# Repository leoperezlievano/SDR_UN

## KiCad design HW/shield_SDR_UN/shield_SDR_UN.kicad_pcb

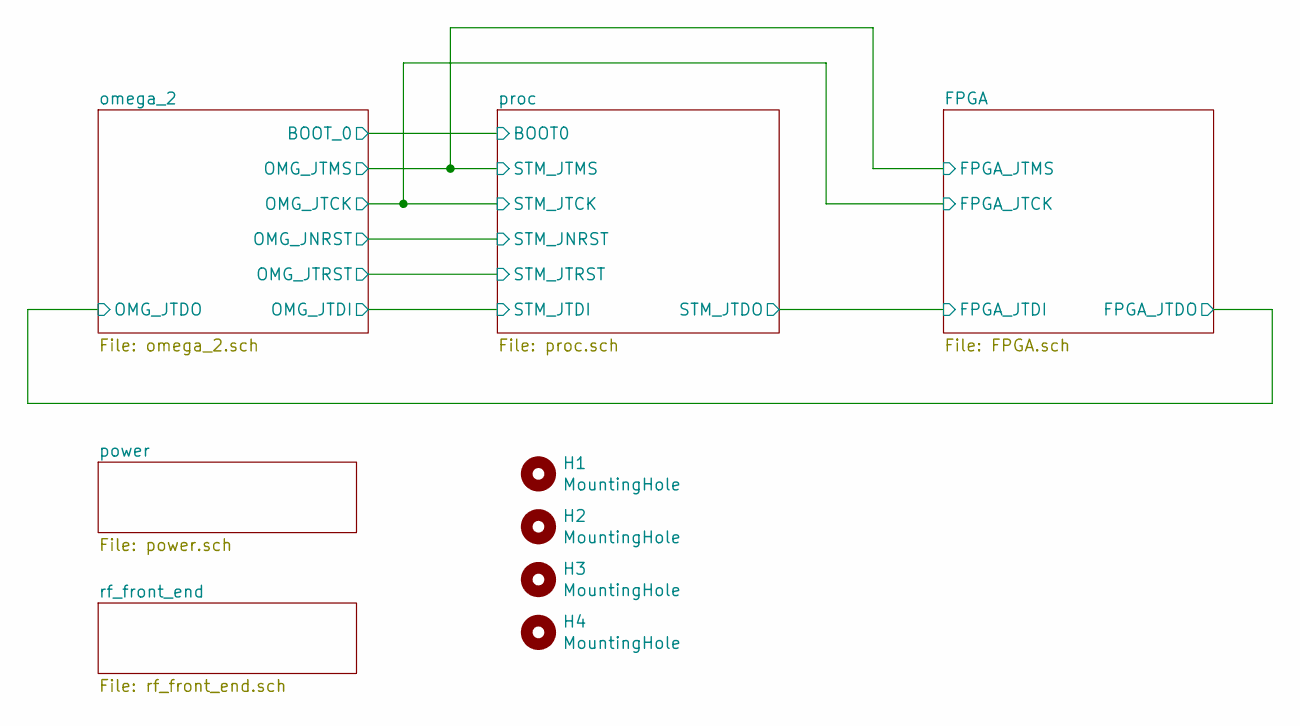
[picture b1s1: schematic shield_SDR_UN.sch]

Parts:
H1, H2, H3, H4: MountingHole; MountingHole_2.7mm_M2.5_ISO14580_Pad

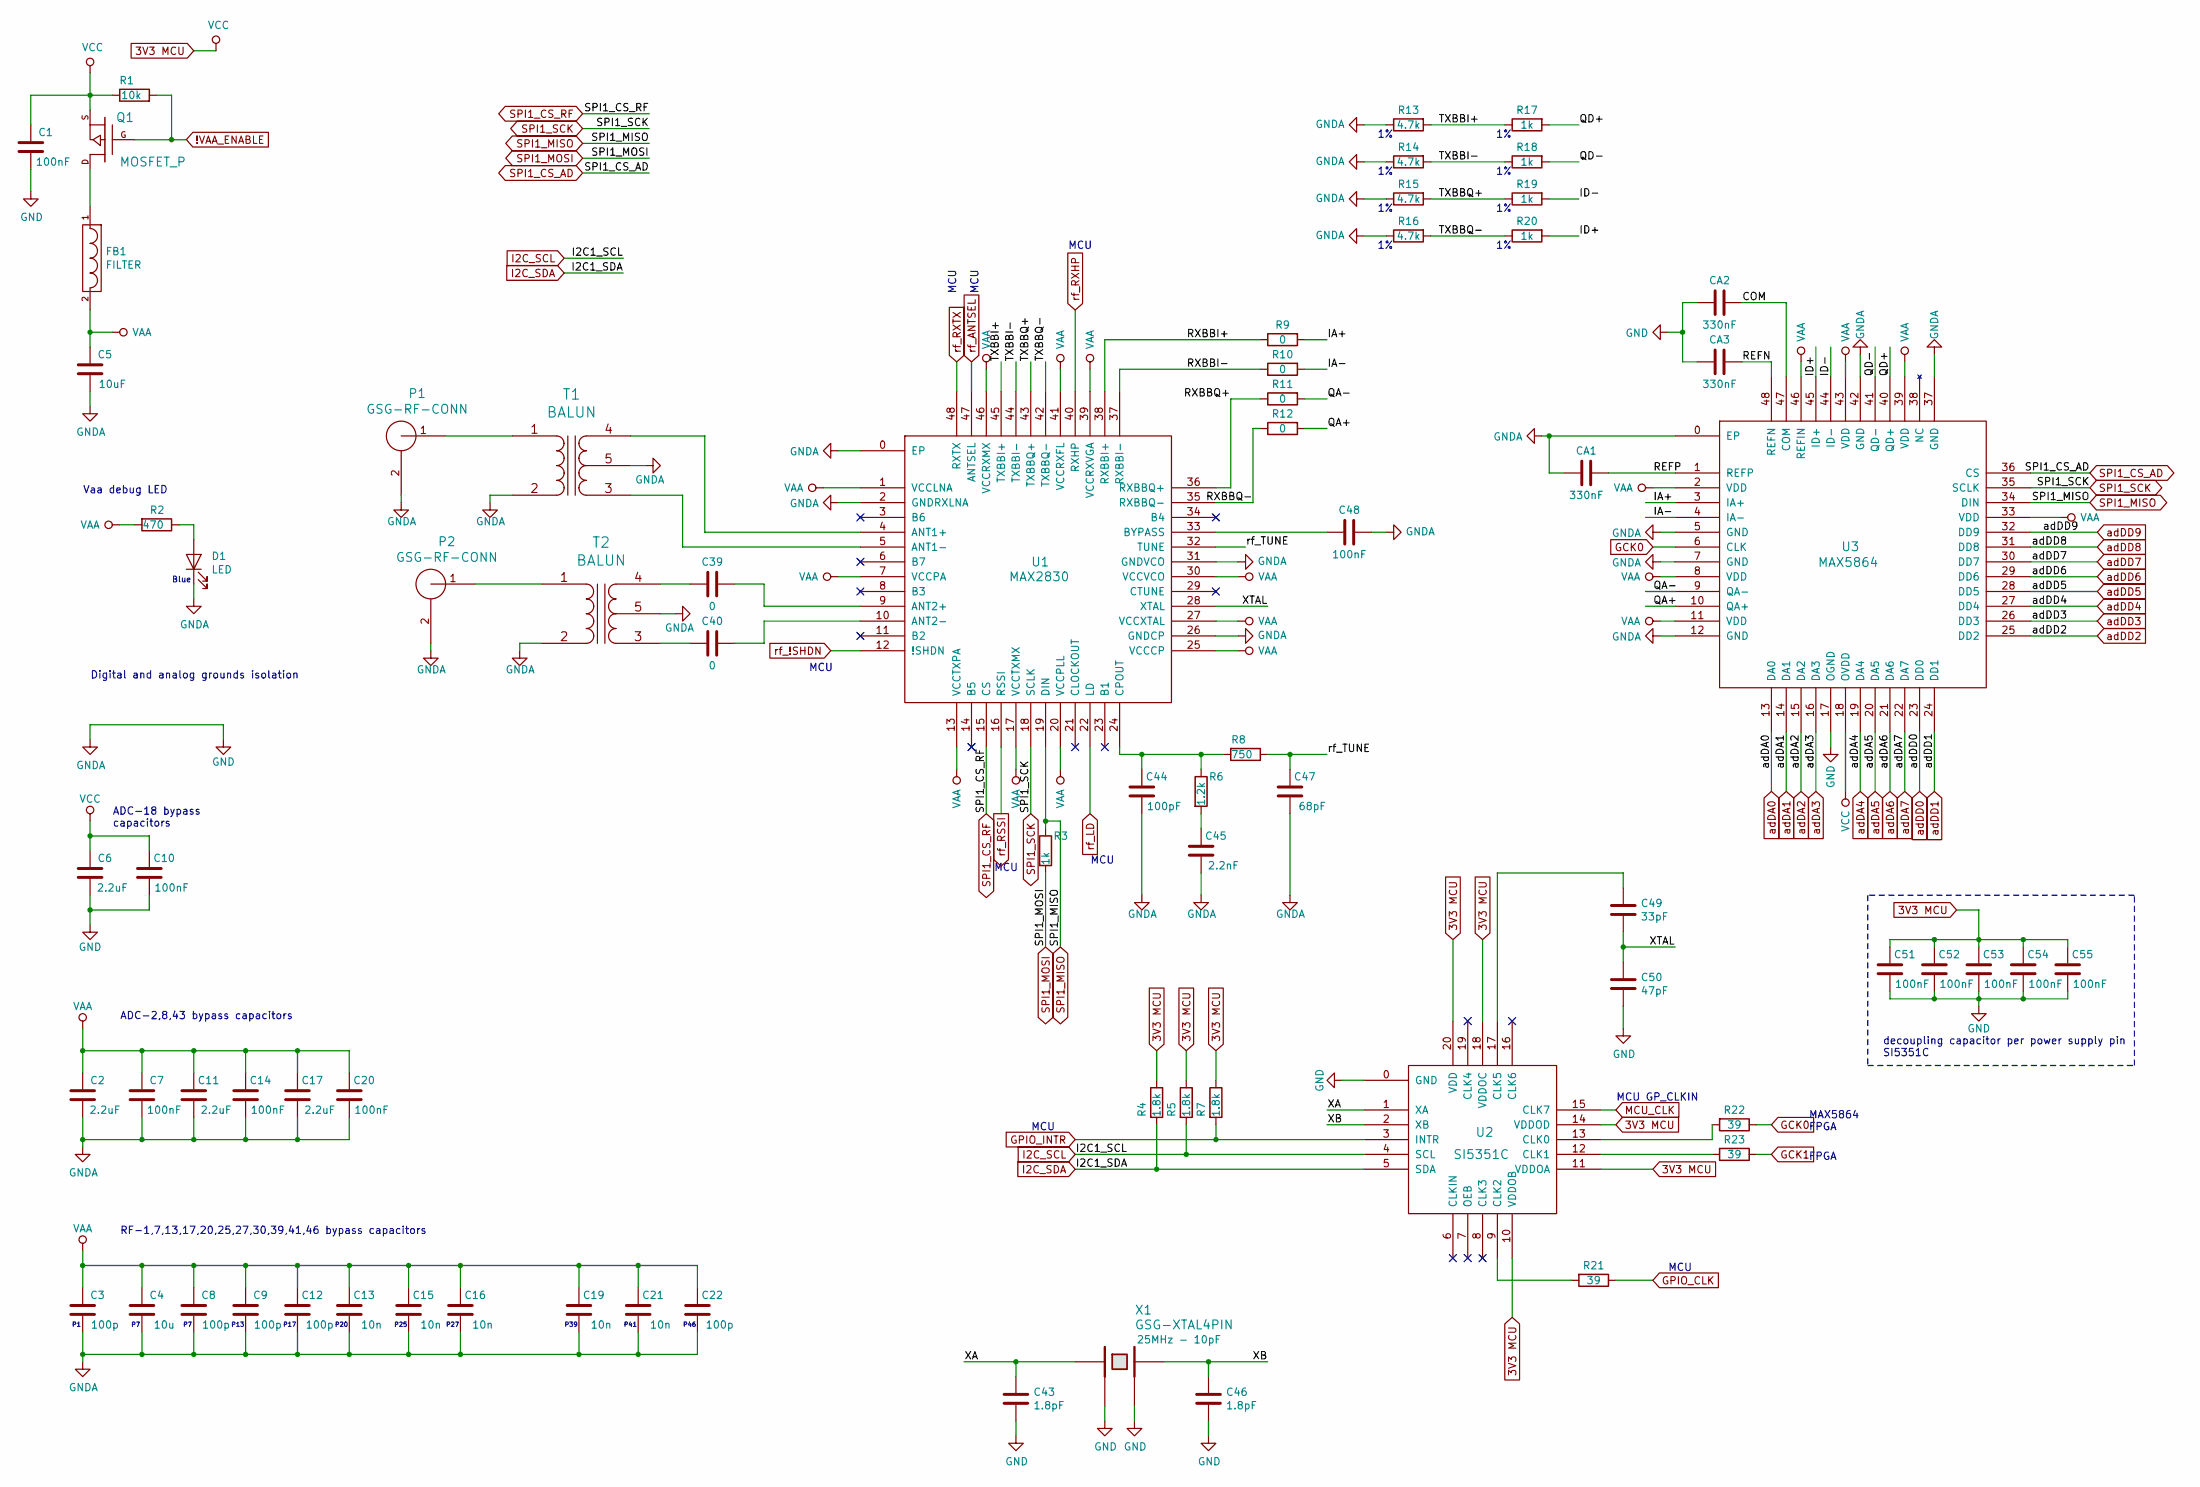
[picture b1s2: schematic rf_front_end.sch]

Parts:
C1, C7, C10, C14, C20, C48, C51, C52, C53, C54, C55: 100nF; C_0603_1608Metric_Pad1.05x0.95mm_HandSolder; Digikey 1276-1000-1-ND
C2, C6, C11, C17: 2.2uF; C_0603_1608Metric_Pad1.05x0.95mm_HandSolder; Digikey 1276-1183-1-ND
C3, C8, C9, C12, C22: 100p; C_0603_1608Metric_Pad1.05x0.95mm_HandSolder; Digikey 1276-1909-1-ND
C4: 10u; C_0603_1608Metric_Pad1.05x0.95mm_HandSolder; Digikey 1276-1192-1-ND
C5: 10uF; C_0603_1608Metric_Pad1.05x0.95mm_HandSolder; Digikey 1276-6456-1-ND
C13, C15, C16, C19, C21: 10n; C_0603_1608Metric_Pad1.05x0.95mm_HandSolder; Digikey 1276-1009-1-ND
C39, C40: 0; C_0402_1005Metric; Digikey 311-0.0JRCT-ND
C43, C46: 1.8pF; C_0603_1608Metric_Pad1.05x0.95mm_HandSolder; Digikey 1276-2218-1-ND
C44: 100pF; C_0603_1608Metric_Pad1.05x0.95mm_HandSolder
C45: 2.2nF; C_0603_1608Metric_Pad1.05x0.95mm_HandSolder; Digikey 1276-1987-1-ND
C47: 68pF; C_0603_1608Metric_Pad1.05x0.95mm_HandSolder
C49: 33pF; C_0603_1608Metric_Pad1.05x0.95mm_HandSolder; Digikey 1276-1070-1-ND
C50: 47pF; C_0603_1608Metric_Pad1.05x0.95mm_HandSolder; Digikey 1276-1037-1-ND
CA1, CA2, CA3: 330nF; C_0603_1608Metric_Pad1.05x0.95mm_HandSolder; Digikey 1276-2048-1-ND
D1: LED; LED_0805_2012Metric_Pad1.15x1.40mm_HandSolder; Digikey 160-2032-1-ND
FB1: FILTER; L_0805_2012Metric_Pad1.15x1.40mm_HandSolder; Digikey BLM21PG221SN1D
P1, P2: GSG-RF-CONN; TAOGLAS_EMPCB.SMAFSTJ.B.HT; Digikey CON-SMA-EDGE-S-ND
Q1: MOSFET_P; SOT103P240X110-3N; Digikey DMP2305UDICT-ND
R1: 10k; R_0603_1608Metric_Pad1.05x0.95mm_HandSolder; Digikey 311-10KGRCT-ND
R2: 470; R_0603_1608Metric_Pad1.05x0.95mm_HandSolder; Digikey 311-470GRCT-ND
R3: 1k; R_0603_1608Metric_Pad1.05x0.95mm_HandSolder
R4, R5, R7: 1.8k; R_0603_1608Metric_Pad1.05x0.95mm_HandSolder; Digikey 311-1.8KGRTR-ND
R6: 1.2k; R_0603_1608Metric_Pad1.05x0.95mm_HandSolder
R8: 750; R_0603_1608Metric_Pad1.05x0.95mm_HandSolder
R9, R10, R11, R12: 0; R_0603_1608Metric_Pad1.05x0.95mm_HandSolder; Digikey RMCF0603ZT0R00CT-ND
R13, R14, R15, R16: 4.7k; R_0603_1608Metric_Pad1.05x0.95mm_HandSolder; Digikey 311-4.70KHRCT-ND
R17, R18, R19, R20: 1k; R_0603_1608Metric_Pad1.05x0.95mm_HandSolder; Digikey 311-1.00KHRCT-ND
R21: 39; R_0603_1608Metric_Pad1.05x0.95mm_HandSolder; part numer RC0603FR-0739RL; digikey 311-39.0HRCT-ND
R22, R23: 39; R_0603_1608Metric_Pad1.05x0.95mm_HandSolder; part numer RC0603FR-0739RL; Digikey 311-39.0HRCT-ND
T1, T2: BALUN; HHM1711E1; Digikey 445-172632-1-ND
U1: MAX2830; MAX2830ETM&plus_; Digikey MAX2830ETM+TCT-ND
U2: SI5351C; QFN50P300X300X60-21N; Digikey 336-5160-1-ND
U3: MAX5864; MAX5864ETM&plus_; Digikey MAX5864ETM+-ND
X1: GSG-XTAL4PIN; GSG-XTAL3.2x2.5mm; Digikey 535-13468-1-ND

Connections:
3V3 MCU: C1.1, C6.1, C10.1, C51.1, C52.1, C53.1, C54.1, C55.1, Q1.S, R1.1, R4.1, R5.1, R7.1, U2.10 (VDDOB), U2.11 (VDDOA), U2.14 (VDDOD), U2.18 (VDDOC), U2.20 (VDD), U3.18 (OVDD); also elsewhere on the board
!VAA_ENABLE: Q1.G, R1.2; also elsewhere on the board
/rf_front_end/COM: CA2.1, U3.47 (COM)
/rf_front_end/IA+: R9.2, U3.3 (IA+)
/rf_front_end/IA-: R10.2, U3.4 (IA-)
/rf_front_end/ID+: R20.2, U3.45 (ID+)
/rf_front_end/ID-: R19.2, U3.44 (ID-)
/rf_front_end/QA+: R12.2, U3.10 (QA+)
/rf_front_end/QA-: R11.2, U3.9 (QA-)
/rf_front_end/QD+: R17.2, U3.40 (QD+)
/rf_front_end/QD-: R18.2, U3.41 (QD-)
/rf_front_end/REFN: CA3.1, U3.48 (REFN)
/rf_front_end/REFP: CA1.1, U3.1 (REFP)
/rf_front_end/RXBBI+: R9.1, U1.38 (RXBBI+)
/rf_front_end/RXBBI-: R10.1, U1.37 (RXBBI-)
/rf_front_end/RXBBQ+: R11.1, U1.36 (RXBBQ+)
/rf_front_end/RXBBQ-: R12.1, U1.35 (RXBBQ-)
/rf_front_end/TXBBI+: R13.2, R17.1, U1.45 (TXBBI+)
/rf_front_end/TXBBI-: R14.2, R18.1, U1.44 (TXBBI-)
/rf_front_end/TXBBQ+: R15.2, R19.1, U1.43 (TXBBQ+)
/rf_front_end/TXBBQ-: R16.2, R20.1, U1.42 (TXBBQ-)
/rf_front_end/XA: C43.1, U2.1 (XA), X1.1
/rf_front_end/XB: C46.1, U2.2 (XB), X1.3
/rf_front_end/XTAL: C49.2, C50.1, U1.28 (XTAL)
/rf_front_end/rf_TUNE: C47.2, R8.1, U1.32 (TUNE)
GCK0: R22.1, U3.6 (CLK); also elsewhere on the board
GCK1: R23.1; also elsewhere on the board
GND: C1.2, C2.2, C3.2, C4.2, C5.2, C6.2, C7.2, C8.2, C9.2, C10.2, C11.2, C12.2, C13.2, C14.2, C15.2, C16.2, C17.2, C19.2, C20.2, C21.2, C22.2, C43.2, C44.1, C45.1, C46.2, C47.1, C48.1, C50.2, C51.2, C52.2, C53.2, C54.2, C55.2, CA1.2, CA2.2, CA3.2, D1.1 (K), P1.2 (GND), P2.2 (GND), R13.1, R14.1, R15.1, R16.1, T1.2 (S2), T1.5 (PM), T2.2 (S2), T2.5 (PM), U1.0 (EP), U1.2 (GNDRXLNA), U1.26 (GNDCP), U1.31 (GNDVCO), U2.0 (GND), U3.0 (EP), U3.5 (GND), U3.7 (GND), U3.12 (GND), U3.17 (OGND), U3.37 (GND), U3.42 (GND), X1.2, X1.4; also elsewhere on the board
GPIO_CLK: R21.1; also elsewhere on the board
GPIO_INTR: R7.2, U2.3 (INTR); also elsewhere on the board
I2C_SCL: R5.2, U2.4 (SCL); also elsewhere on the board
I2C_SDA: R4.2, U2.5 (SDA); also elsewhere on the board
MCU_CLK: U2.15 (CLK7); also elsewhere on the board
unnamed: C39.1, U1.9 (ANT2+)
unnamed: C39.2, T2.4 (PR2)
unnamed: C40.1, U1.10 (ANT2-)
unnamed: C40.2, T2.3 (PR1)
unnamed: C44.2, R6.1, R8.2, U1.24 (CPOUT)
unnamed: C45.2, R6.2
unnamed: C48.2, U1.33 (BYPASS)
unnamed: C49.1, U2.17 (CLK5)
unnamed: D1.2 (A), R2.1
unnamed: FB1.1, Q1.D
unnamed: P1.1 (RF), T1.1 (S1)
unnamed: P2.1 (RF), T2.1 (S1)
unnamed: R21.2, U2.9 (CLK2)
unnamed: R22.2, U2.13 (CLK0)
unnamed: R23.2, U2.12 (CLK1)
unnamed: T1.3 (PR1), U1.5 (ANT1-)
unnamed: T1.4 (PR2), U1.4 (ANT1+)
SPI1_CS_AD: U3.36 (CS); also elsewhere on the board
SPI1_CS_RF: U1.15 (CS); also elsewhere on the board
SPI1_MISO: R3.1, U1.19 (DIN), U3.34 (DIN); also elsewhere on the board
SPI1_MOSI: R3.2; also elsewhere on the board
SPI1_SCK: U1.18 (SCLK), U3.35 (SCLK); also elsewhere on the board
VAA: C2.1, C3.1, C4.1, C5.1, C7.1, C8.1, C9.1, C11.1, C12.1, C13.1, C14.1, C15.1, C16.1, C17.1, C19.1, C20.1, C21.1, C22.1, FB1.2, R2.2, U1.1 (VCCLNA), U1.7 (VCCPA), U1.13 (VCCTXPA), U1.17 (VCCTXMX), U1.20 (VCCPLL), U1.25 (VCCCP), U1.27 (VCCXTAL), U1.30 (VCCVCO), U1.39 (VCCRXVGA), U1.41 (VCCRXFL), U1.46 (VCCRXMX), U3.2 (VDD), U3.8 (VDD), U3.11 (VDD), U3.33 (VDD), U3.39 (VDD), U3.43 (VDD), U3.46 (REFIN)
adDA0: U3.13 (DA0); also elsewhere on the board
adDA1: U3.14 (DA1); also elsewhere on the board
adDA2: U3.15 (DA2); also elsewhere on the board
adDA3: U3.16 (DA3); also elsewhere on the board
adDA4: U3.19 (DA4); also elsewhere on the board
adDA5: U3.20 (DA5); also elsewhere on the board
adDA6: U3.21 (DA6); also elsewhere on the board
adDA7: U3.22 (DA7); also elsewhere on the board
adDD0: U3.23 (DD0); also elsewhere on the board
adDD1: U3.24 (DD1); also elsewhere on the board
adDD2: U3.25 (DD2); also elsewhere on the board
adDD3: U3.26 (DD3); also elsewhere on the board
adDD4: U3.27 (DD4); also elsewhere on the board
adDD5: U3.28 (DD5); also elsewhere on the board
adDD6: U3.29 (DD6); also elsewhere on the board
adDD7: U3.30 (DD7); also elsewhere on the board
adDD8: U3.31 (DD8); also elsewhere on the board
adDD9: U3.32 (DD9); also elsewhere on the board
rf_!SHDN: U1.12 (!SHDN); also elsewhere on the board
rf_ANTSEL: U1.47 (ANTSEL); also elsewhere on the board
rf_LD: U1.22 (LD); also elsewhere on the board
rf_RSSI: U1.16 (RSSI); also elsewhere on the board
rf_RXHP: U1.40 (RXHP); also elsewhere on the board
rf_RXTX: U1.48 (RXTX); also elsewhere on the board

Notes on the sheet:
ADC-18 bypass capacitors
ADC-2,8,43 bypass capacitors
Vaa debug LED
Digital and analog grounds isolation
RF-1,7,13,17,20,25,27,30,39,41,46 bypass capacitors
MCU
FPGA
MAX5864 FPGA
MCU GP_CLKIN
Blue
decoupling capacitor per power supply pin SI5351C
MCU
P13
P17
P20
P25
P27
P39
P41
P46

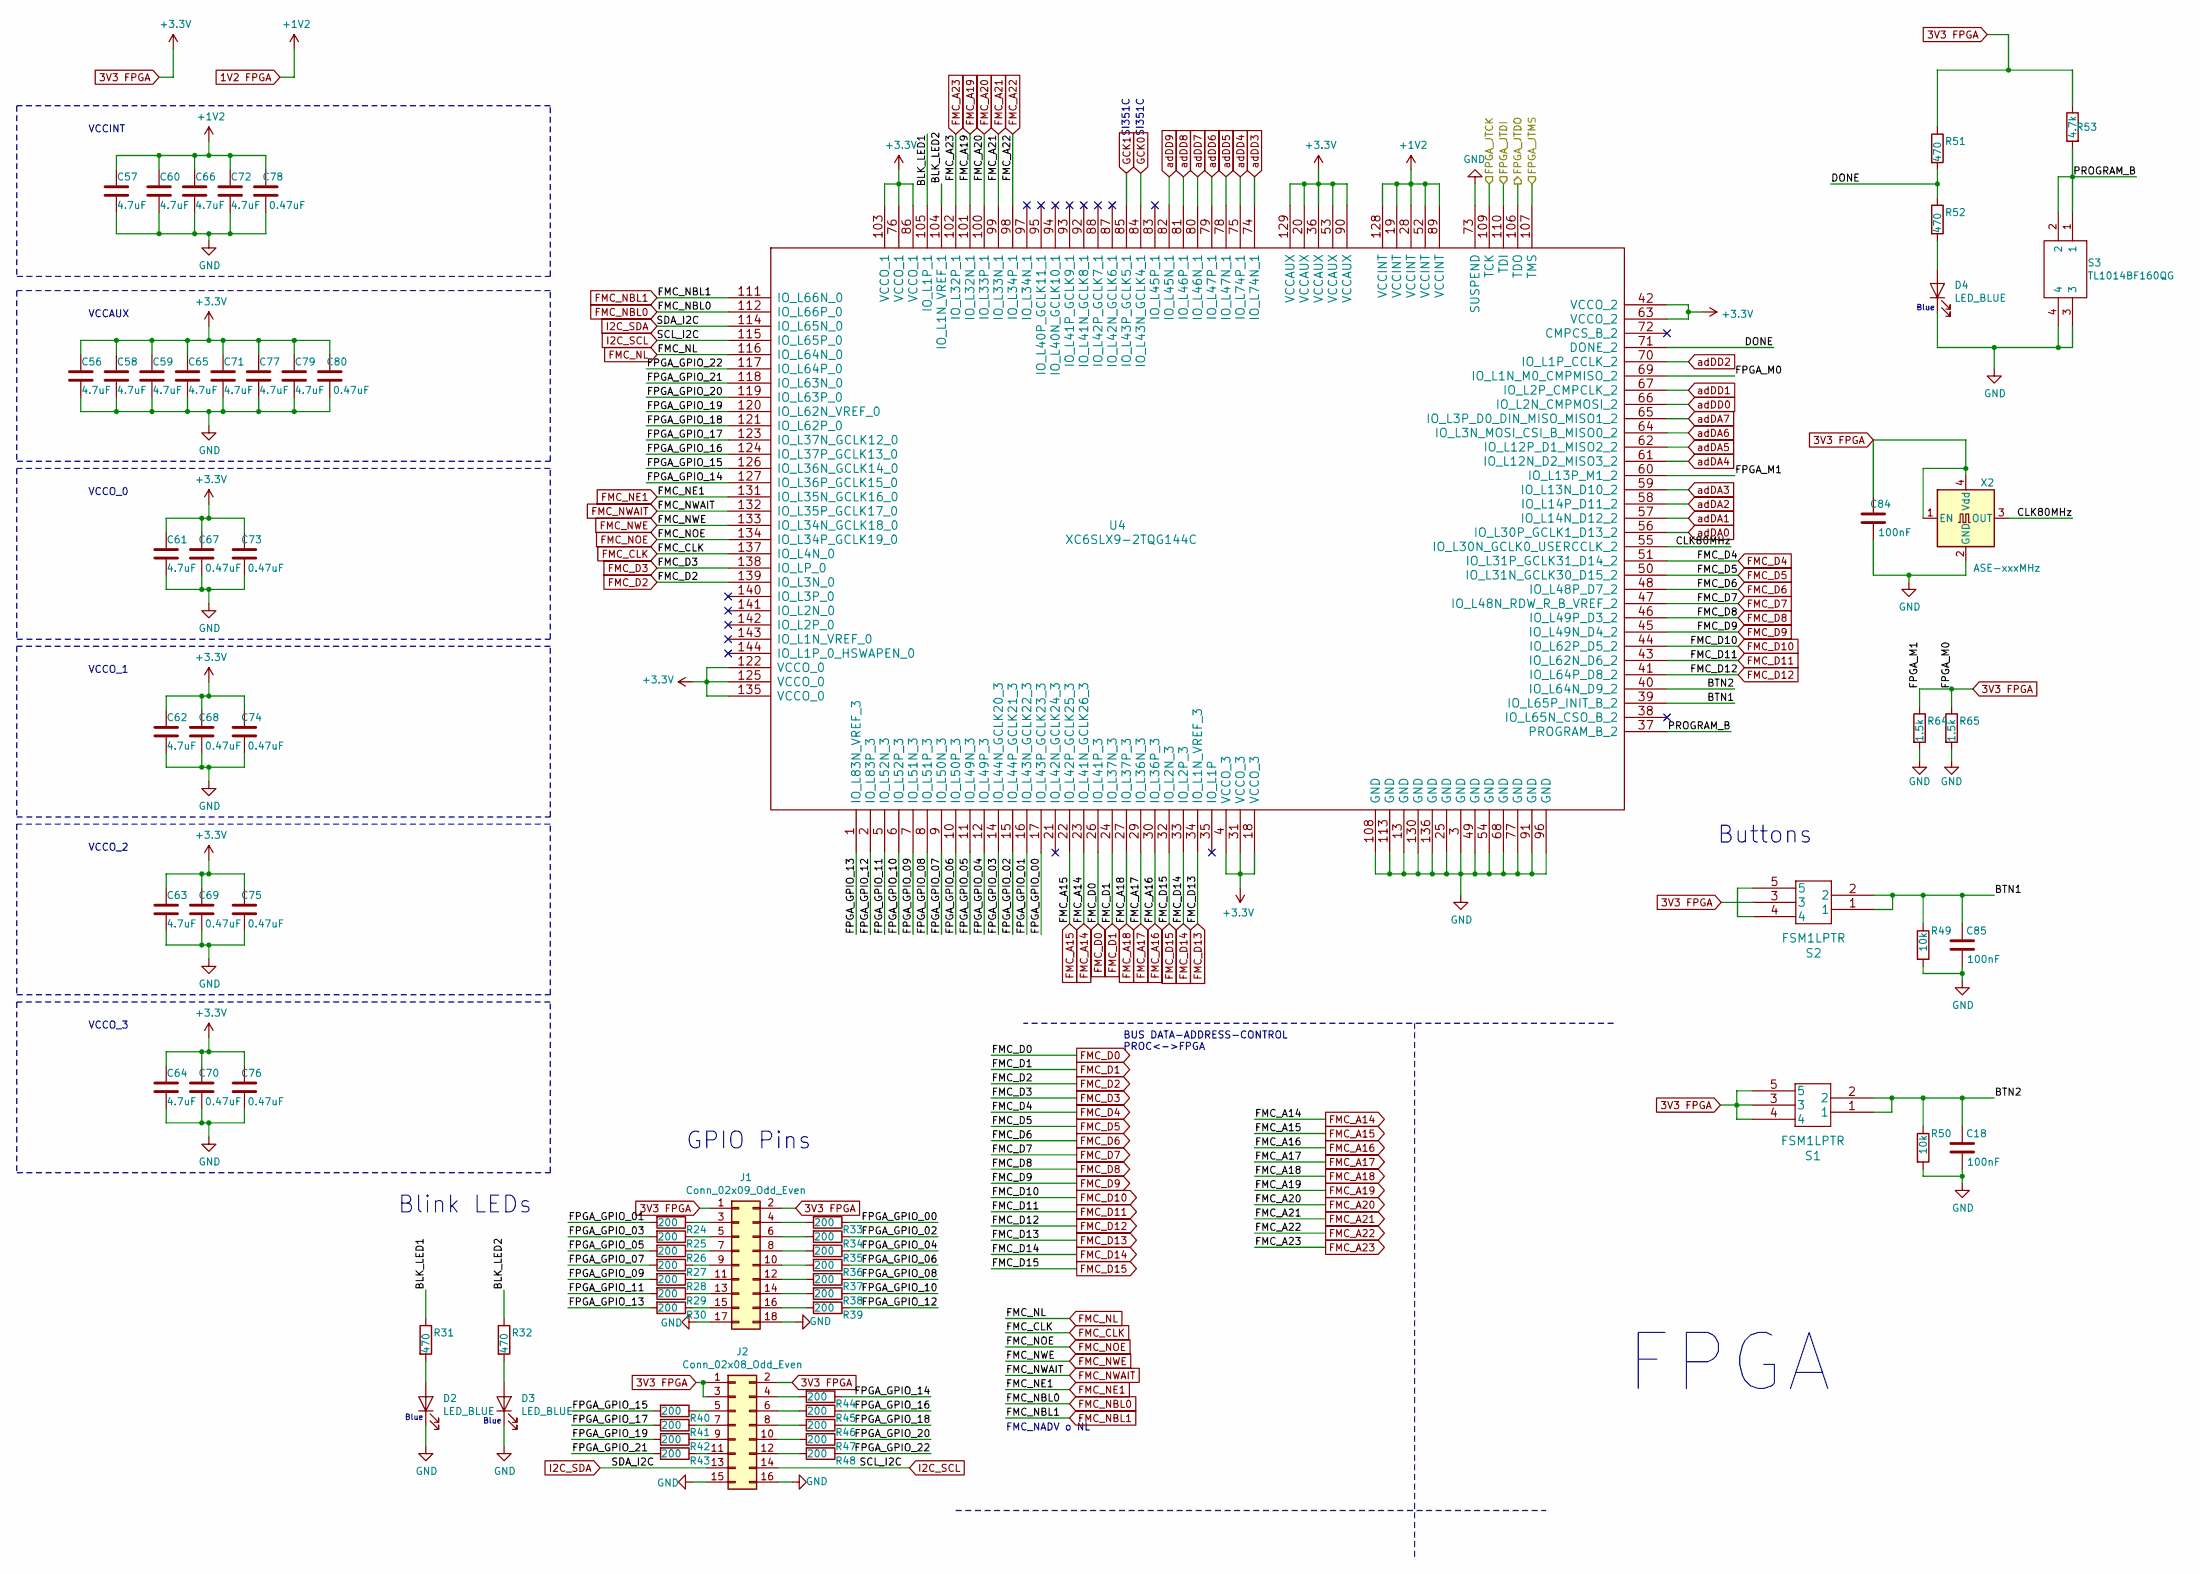
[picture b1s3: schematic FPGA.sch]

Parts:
C18, C84, C85: 100nF; C_0603_1608Metric_Pad1.05x0.95mm_HandSolder; Digikey 1276-1000-1-ND
C56, C57, C58, C59, C60, C61, C62, C63, C64, C65, C66, C71, C72, C77, C79: 4.7uF; C_0603_1608Metric_Pad1.05x0.95mm_HandSolder; Digikey 1276-1045-1-ND
C67, C68, C69, C70, C73, C74, C75, C76, C78, C80: 0.47uF; C_0603_1608Metric_Pad1.05x0.95mm_HandSolder; Digikey 1276-2082-1-ND
D2, D3, D4: LED_BLUE; LED_0805_2012Metric_Pad1.15x1.40mm_HandSolder; Digikey 160-2032-1-ND
J1: Conn_02x09_Odd_Even; PinHeader_2x09_P2.54mm_Vertical; Digikey 609-6336-ND
J2: Conn_02x08_Odd_Even; PinHeader_2x08_P2.54mm_Vertical; Digikey 609-6336-ND
R24, R25, R26, R27, R28, R29, R30, R33, R34, R35, R36, R37, R38, R39, R40, R41, R42, R43, R44, R45, R46, R47, R48: 200; R_0603_1608Metric_Pad1.05x0.95mm_HandSolder; Digikey 311-200GRCT-ND
R31, R32, R51, R52: 470; R_0603_1608Metric_Pad1.05x0.95mm_HandSolder; Digikey 311-470GRCT-ND
R49, R50: 10k; R_0603_1608Metric_Pad1.05x0.95mm_HandSolder; Digikey 311-10KGRCT-ND
R53: 4.7k; R_0603_1608Metric_Pad1.05x0.95mm_HandSolder; Digikey 311-4.70KHRCT-ND
R64, R65: 1.5k; R_0603_1608Metric_Pad1.05x0.95mm_HandSolder; Digikey 311-1.5KGRCT-ND
S1, S2: FSM1LPTR; Digikey 450-1756-1-ND
S3: TL1014BF160QG; Digikey EG5042CT-ND
U4: XC6SLX9-2TQG144C; LQFP-144_20x20mm_P0.5mm; Digikey 122-1745-ND
X2: ASE-xxxMHz; Oscillator_SMD_Abracon_ASE-4Pin_3.2x2.5mm_HandSoldering; Digikey 535-11114-1-ND

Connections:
1V2 FPGA: C57.1, C60.1, C66.1, C72.1, C78.1, U4.19 (VCCINT), U4.28 (VCCINT), U4.52 (VCCINT), U4.89 (VCCINT), U4.128 (VCCINT); also elsewhere on the board
3V3 FPGA: C56.1, C58.1, C59.1, C61.1, C62.1, C63.1, C64.1, C65.1, C67.1, C68.1, C69.1, C70.1, C71.1, C73.1, C74.1, C75.1, C76.1, C77.1, C79.1, C80.1, C84.1, J1.1, J1.2, J2.1, J2.2, J2.3, R51.1, R53.1, R64.1, R65.1, S1.3, S1.4, S1.5, S2.3, U4.4 (VCCO_3), U4.18 (VCCO_3), U4.20 (VCCAUX), U4.31 (VCCO_3), U4.36 (VCCAUX), U4.42 (VCCO_2), U4.53 (VCCAUX), U4.60 (IO_L13P_M1_2), U4.63 (VCCO_2), U4.69 (IO_L1N_M0_CMPMISO_2), U4.76 (VCCO_1), U4.86 (VCCO_1), U4.90 (VCCAUX), U4.103 (VCCO_1), U4.122 (VCCO_0), U4.125 (VCCO_0), U4.129 (VCCAUX), U4.135 (VCCO_0), X2.1 (EN), X2.4 (Vdd); also elsewhere on the board
/FPGA/BLK_LED1: R31.1, U4.105 (IO_L1P_1)
/FPGA/BLK_LED2: R32.1, U4.104 (IO_L1N_VREF_1)
/FPGA/BTN1: C85.1, R49.1, S2.1, S2.2, U4.39 (IO_L65P_INIT_B_2)
/FPGA/BTN2: C18.1, R50.1, S1.1, S1.2, U4.40 (IO_L64N_D9_2)
/FPGA/CLK80MHz: U4.55 (IO_L30N_GCLK0_USERCCLK_2), X2.3 (OUT)
/FPGA/DONE: R51.2, R52.1, U4.71 (DONE_2)
/FPGA/FPGA_GPIO_00: R33.1, U4.17 (IO_L43P_GCLK23_3)
/FPGA/FPGA_GPIO_01: R24.2, U4.16 (IO_L43N_GCLK22_3)
/FPGA/FPGA_GPIO_02: R34.1, U4.15 (IO_L44P_GCLK21_3)
/FPGA/FPGA_GPIO_03: R25.2, U4.14 (IO_L44N_GCLK20_3)
/FPGA/FPGA_GPIO_04: R35.1, U4.12 (IO_L49P_3)
/FPGA/FPGA_GPIO_05: R26.2, U4.11 (IO_L49N_3)
/FPGA/FPGA_GPIO_06: R36.1, U4.10 (IO_L50P_3)
/FPGA/FPGA_GPIO_07: R27.2, U4.9 (IO_L50N_3)
/FPGA/FPGA_GPIO_08: R37.1, U4.8 (IO_L51P_3)
/FPGA/FPGA_GPIO_09: R28.2, U4.7 (IO_L51N_3)
/FPGA/FPGA_GPIO_10: R38.1, U4.6 (IO_L52P_3)
/FPGA/FPGA_GPIO_11: R29.2, U4.5 (IO_L52N_3)
/FPGA/FPGA_GPIO_12: R39.1, U4.2 (IO_L83P_3)
/FPGA/FPGA_GPIO_13: R30.2, U4.1 (IO_L83N_VREF_3)
/FPGA/FPGA_GPIO_14: R44.1, U4.127 (IO_L36P_GCLK15_0)
/FPGA/FPGA_GPIO_15: R40.2, U4.126 (IO_L36N_GCLK14_0)
/FPGA/FPGA_GPIO_16: R45.1, U4.124 (IO_L37P_GCLK13_0)
/FPGA/FPGA_GPIO_17: R41.2, U4.123 (IO_L37N_GCLK12_0)
/FPGA/FPGA_GPIO_18: R46.1, U4.121 (IO_L62P_0)
/FPGA/FPGA_GPIO_19: R42.2, U4.120 (IO_L62N_VREF_0)
/FPGA/FPGA_GPIO_20: R47.1, U4.119 (IO_L63P_0)
/FPGA/FPGA_GPIO_21: R43.2, U4.118 (IO_L63N_0)
/FPGA/FPGA_GPIO_22: R48.1, U4.117 (IO_L64P_0)
/FPGA/PROGRAM_B: R53.2, S3.1, S3.2, U4.37 (PROGRAM_B_2)
/FPGA_JTDO: U4.106 (TDO); also elsewhere on the board
/OMG_JTCK: U4.109 (TCK); also elsewhere on the board
/OMG_JTMS: U4.107 (TMS); also elsewhere on the board
/STM_JTDO: U4.110 (TDI); also elsewhere on the board
FMC_A14: U4.23 (IO_L41N_GCLK26_3); also elsewhere on the board
FMC_A15: U4.22 (IO_L42P_GCLK25_3); also elsewhere on the board
FMC_A16: U4.30 (IO_L36P_3); also elsewhere on the board
FMC_A17: U4.29 (IO_L36N_3); also elsewhere on the board
FMC_A18: U4.27 (IO_L37P_3); also elsewhere on the board
FMC_A19: U4.101 (IO_L32N_1); also elsewhere on the board
FMC_A20: U4.100 (IO_L33P_1); also elsewhere on the board
FMC_A21: U4.99 (IO_L33N_1); also elsewhere on the board
FMC_A22: U4.98 (IO_L34P_1); also elsewhere on the board
FMC_A23: U4.102 (IO_L32P_1); also elsewhere on the board
FMC_CLK: U4.137 (IO_L4N_0); also elsewhere on the board
FMC_D0: U4.26 (IO_L41P_3); also elsewhere on the board
FMC_D1: U4.24 (IO_L37N_3); also elsewhere on the board
FMC_D2: U4.139 (IO_L3N_0); also elsewhere on the board
FMC_D3: U4.138 (IO_LP_0); also elsewhere on the board
FMC_D4: U4.51 (IO_L31P_GCLK31_D14_2); also elsewhere on the board
FMC_D5: U4.50 (IO_L31N_GCLK30_D15_2); also elsewhere on the board
FMC_D6: U4.48 (IO_L48P_D7_2); also elsewhere on the board
FMC_D7: U4.47 (IO_L48N_RDW_R_B_VREF_2); also elsewhere on the board
FMC_D8: U4.46 (IO_L49P_D3_2); also elsewhere on the board
FMC_D9: U4.45 (IO_L49N_D4_2); also elsewhere on the board
FMC_D10: U4.44 (IO_L62P_D5_2); also elsewhere on the board
FMC_D11: U4.43 (IO_L62N_D6_2); also elsewhere on the board
FMC_D12: U4.41 (IO_L64P_D8_2); also elsewhere on the board
FMC_D13: U4.34 (IO_L1N_VREF_3); also elsewhere on the board
FMC_D14: U4.33 (IO_L2P_3); also elsewhere on the board
FMC_D15: U4.32 (IO_L2N_3); also elsewhere on the board
FMC_NBL0: U4.112 (IO_L66P_0); also elsewhere on the board
FMC_NBL1: U4.111 (IO_L66N_0); also elsewhere on the board
FMC_NE1: U4.131 (IO_L35N_GCLK16_0); also elsewhere on the board
FMC_NL: U4.116 (IO_L64N_0); also elsewhere on the board
FMC_NOE: U4.134 (IO_L34P_GCLK19_0); also elsewhere on the board
FMC_NWAIT: U4.132 (IO_L35P_GCLK17_0); also elsewhere on the board
FMC_NWE: U4.133 (IO_L34N_GCLK18_0); also elsewhere on the board
GCK0: U4.84 (IO_L43N_GCLK4_1); also elsewhere on the board
GCK1: U4.85 (IO_L43P_GCLK5_1); also elsewhere on the board
GND: C18.2, C56.2, C57.2, C58.2, C59.2, C60.2, C61.2, C62.2, C63.2, C64.2, C65.2, C66.2, C67.2, C68.2, C69.2, C70.2, C71.2, C72.2, C73.2, C74.2, C75.2, C76.2, C77.2, C78.2, C79.2, C80.2, C84.2, C85.2, D2.1 (K), D3.1 (K), D4.1 (K), J1.17, J1.18, J2.15, J2.16, R49.2, R50.2, R64.2, R65.2, S3.3, S3.4, U4.3 (GND), U4.13 (GND), U4.25 (GND), U4.49 (GND), U4.54 (GND), U4.68 (GND), U4.73 (SUSPEND), U4.77 (GND), U4.91 (GND), U4.96 (GND), U4.108 (GND), U4.113 (GND), U4.130 (GND), U4.136 (GND), X2.2 (GND); also elsewhere on the board
I2C_SCL: J2.14, U4.115 (IO_L65P_0); also elsewhere on the board
I2C_SDA: J2.13, U4.114 (IO_L65N_0); also elsewhere on the board
unnamed: D2.2 (A), R31.2
unnamed: D3.2 (A), R32.2
unnamed: D4.2 (A), R52.2
unnamed: J1.3, R24.1
unnamed: J1.4, R33.2
unnamed: J1.5, R25.1
unnamed: J1.6, R34.2
unnamed: J1.7, R26.1
unnamed: J1.8, R35.2
unnamed: J1.9, R27.1
unnamed: J1.10, R36.2
unnamed: J1.11, R28.1
unnamed: J1.12, R37.2
unnamed: J1.13, R29.1
unnamed: J1.14, R38.2
unnamed: J1.15, R30.1
unnamed: J1.16, R39.2
unnamed: J2.4, R44.2
unnamed: J2.5, R40.1
unnamed: J2.6, R45.2
unnamed: J2.7, R41.1
unnamed: J2.8, R46.2
unnamed: J2.9, R42.1
unnamed: J2.10, R47.2
unnamed: J2.11, R43.1
unnamed: J2.12, R48.2
unnamed: S2.4, S2.5
adDA0: U4.56 (IO_L30P_GCLK1_D13_2); also elsewhere on the board
adDA1: U4.57 (IO_L14N_D12_2); also elsewhere on the board
adDA2: U4.58 (IO_L14P_D11_2); also elsewhere on the board
adDA3: U4.59 (IO_L13N_D10_2); also elsewhere on the board
adDA4: U4.61 (IO_L12N_D2_MISO3_2); also elsewhere on the board
adDA5: U4.62 (IO_L12P_D1_MISO2_2); also elsewhere on the board
adDA6: U4.64 (IO_L3N_MOSI_CSI_B_MISO0_2); also elsewhere on the board
adDA7: U4.65 (IO_L3P_D0_DIN_MISO_MISO1_2); also elsewhere on the board
adDD0: U4.66 (IO_L2N_CMPMOSI_2); also elsewhere on the board
adDD1: U4.67 (IO_L2P_CMPCLK_2); also elsewhere on the board
adDD2: U4.70 (IO_L1P_CCLK_2); also elsewhere on the board
adDD3: U4.74 (IO_L74N_1); also elsewhere on the board
adDD4: U4.75 (IO_L74P_1); also elsewhere on the board
adDD5: U4.78 (IO_L47N_1); also elsewhere on the board
adDD6: U4.79 (IO_L47P_1); also elsewhere on the board
adDD7: U4.80 (IO_L46N_1); also elsewhere on the board
adDD8: U4.81 (IO_L46P_1); also elsewhere on the board
adDD9: U4.82 (IO_L45N_1); also elsewhere on the board

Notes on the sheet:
FPGA
Blink LEDs
GPIO Pins
BUS DATA-ADDRESS-CONTROL PROC<->FPGA
Blue
SI351C
Buttons
FMC_NADV o NL
VCCINT
VCCAUX
VCCO_0
VCCO_1
VCCO_2
VCCO_3

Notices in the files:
parts and their libraries:
Copyright 2016 Accelerated Designs. All rights reserved.
